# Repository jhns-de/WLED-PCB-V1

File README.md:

# WLED PCB V1

This PCB is outdated and I can no longer recommend using it. Please use [WLED-PCB-V2](https://github.com/jhns-de/WLED-PCB-V2) instead. It has much more safety features.

## Summary
This is a PCB to control a 12V [GS8208](http://www.normandled.com/upload/201805/GS8208%20LED%20Datasheet.pdf) LED Stripe with [WLED](https://github.com/Aircoookie/WLED).
The PCB contains a voltage regulator to provide 5V for the Wemos D1 mini and a level shifter for the signal line.
Furthermore, the PCB is designed so that it goes directly inbetween the power supply and the LED Stripe.

This project is for an external ambilight solution for a VESA mounted monitor. Therefore the width of the PCB is given by the L-profile where the PCB is mounted on.

**This PCB was designed in [KiCad](https://www.kicad.org/).**

## Schematic

### Partlist

| Quantity | Reference | Part | Footprint | Function |
|----------|-----------|------|-----------|----------|
| 2  | C1, C2 | 1u Capacitor | D5.00mm P2.00mm | voltage smoothing |
| 3 | C3, C4, C6 | 100n Capacitor | L7.0mm P5.00mm | voltage smoothing |
| 1 | C5 | 300n Capacitor | L7.00mm P5.00mm | voltage smoothing |
| 2 | D1, D2 | 5mm LED |  | Check if 12V and 5V are available |
| 1 | D3 | 1N5817 Diode |  | reverse polarity protection |
| 2 | R1, R2 | 1k Resistor | L3.6mm THT | series resistor for LED |
| 1 | R3 | 470R Resistor | L3.6mm THT | series resistor for data line |
| 1 | U1 | LM7805 | TO-220 | voltage regulator |
| 1 | U2 | SN74AHCT125N | DIP-14 | levelshifter for data line |
| 1 | U3 | WeMos D1 Mini |  | Controller |

### Recommended Parts

**These are the parts I used.**
*The following links are affiliate links!*

- [1u Capacitor](https://amzn.to/3BVUkxN)
- [100n Capacitor](https://amzn.to/3lNCLui)
- [1N5817 Diode](https://amzn.to/3vk3HEU)
- [LM7805](https://amzn.to/3pdkVmA)
- [SN74AHCT125](https://amzn.to/3jerAca)
- [WeMos D1 Mini **compatible board**](https://amzn.to/2Z43ZnQ)

## PCB

Order the PCB [here](https://www.pcbway.com/project/shareproject/WLED_PCB_V1.html) from PCBWay.

### Front

### Back

## Images

## License

This project is licensed under the GNU GPLv3.

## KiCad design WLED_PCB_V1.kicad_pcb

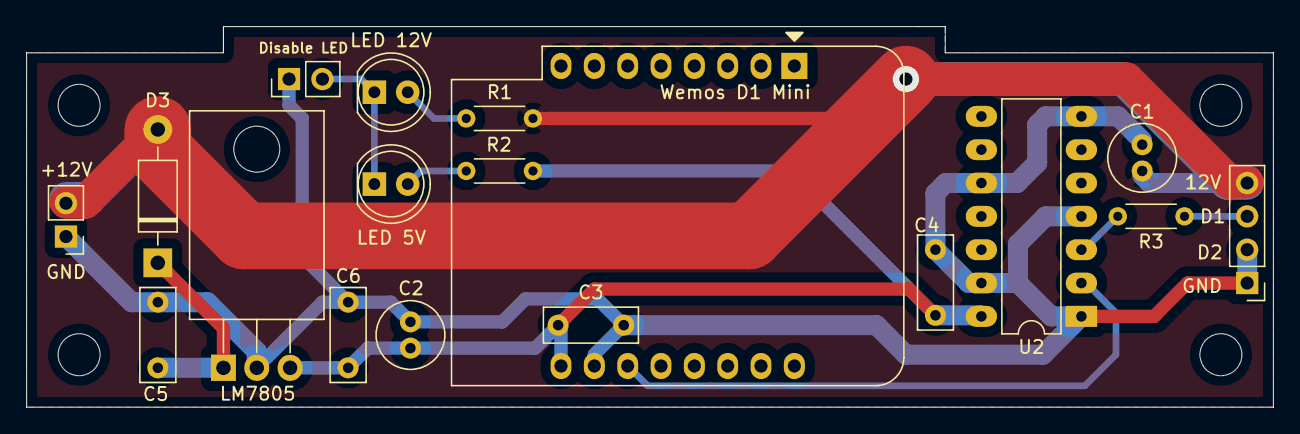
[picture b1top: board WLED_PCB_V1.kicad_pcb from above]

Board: 2 copper layers, 95.0 x 29.0 mm, 18 parts (0 on the bottom side), 10 nets.

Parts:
C1, C2: 1µ; C_Radial_D5.0mm_H11.0mm_P2.00mm
C3, C4, C6: 100n; C_Rect_L7.0mm_W2.5mm_P5.00mm
C5: 300n; C_Rect_L7.0mm_W2.5mm_P5.00mm
D3: 1N5817; D_DO-41_SOD81_P10.16mm_Horizontal
Disable LED: Jumper; PinHeader_1x02_P2.54mm_Vertical
LED 5V: LED 5V; LED_D5.0mm_Clear
LED 12V: LED 12V; LED_D5.0mm_Clear
LED_Conn1: Conn_01x04; PinHeader_1x04_P2.54mm_Vertical
LM7805: LM7805; TO-220-3_Horizontal_TabDown
PWR: Conn_01x02; PinHeader_1x02_P2.54mm_Vertical
R1, R2: 1k; R_Axial_DIN0204_L3.6mm_D1.6mm_P5.08mm_Horizontal
R3: 470R; R_Axial_DIN0204_L3.6mm_D1.6mm_P5.08mm_Horizontal
U2: SN74AHCT125N; DIP-14_W7.62mm_LongPads
Wemos D1 Mini: WeMos_D1_mini; WEMOS_D1_mini_light

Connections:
+5V: C2.1, C3.1, C4.1, C6.1, LM7805.3, R2.1, U2.14, Wemos D1 Mini.9
+12V: C1.1, D3.2, LED_Conn1.4, PWR.2, R1.1
GND: C1.2, C2.2, C3.2, C4.2, C5.2, C6.2, Disable LED.1, LED_Conn1.1, LED_Conn1.2, LM7805.2, PWR.1, U2.1, U2.4, U2.7, U2.10, U2.13, Wemos D1 Mini.10
unnamed: C5.1, D3.1, LM7805.1
unnamed: Disable LED.2, LED 5V.1, LED 12V.1
unnamed: LED 12V.2, R1.2
unnamed: LED 5V.2, R2.2
unnamed: LED_Conn1.3, R3.1
unnamed: R3.2, U2.3
unnamed: U2.2, Wemos D1 Mini.11

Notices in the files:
WLED_PCB_V1.kicad_pcb:
Licensed under GNU GPLv3
